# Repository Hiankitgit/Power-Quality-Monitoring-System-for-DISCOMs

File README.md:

# Power Quality Monitoring System for DISCOMs

## 📌 Overview
A low-cost, embedded diagnostic node designed for electricity distribution networks (DISCOMs). This system is engineered to detect sub-threshold power quality anomalies that are typically invisible to conventional protection devices. 

The hardware acts as a unified motherboard, integrating microcontrollers, analog voltage sensing, and industrial RS-485 communication into a single robust node.

## 🔌 Hardware Architecture
The custom PCB functions as a docking station utilizing pre-built modules and discrete through-hole components:
*   **Microcontrollers:** Arduino Uno & STM32 Blue Pill
*   **Voltage Sensing:** ZMPT101B AC voltage transformer module
*   **Communication:** MAX485 (TTL-to-RS485 transceiver) for node-level fault reporting
*   **Safety Infrastructure:** 220V AC mains are wired directly into the ZMPT module terminals, keeping high-voltage traces entirely isolated from the custom 5V logic board.

## 🛠️ PCB Design & Fabrication
Designed entirely in **KiCad**, the board layout was heavily optimized for DIY in-house manufacturing.
*   **Clearances & Traces:** Passed stringent DRC with 0.2mm minimum clearance. Main 5V and GND power rails are thickened (0.8mm) to prevent voltage drops across the docked modules.
*   **Routing Logic:** Verified intermediate node routing (including daisy-chained parallel capacitors) with 45-degree smoothed traces to prevent acid traps.
*   **Fabrication Method:** Specifically routed to support the **toner transfer etching** method on a blank copper clad board. A 1:1 scale mirrored PDF and standard Gerber `.zip` are provided in the `/fabrication` directory.

## 🖼️ Board Previews

# 💻 Firmware: Power Quality Monitoring Node

⚠️ **Status: Work In Progress (Fine-Tuning Phase)**

This directory contains the source code for the Arduino Uno and STM32 microcontrollers. 

### Current Development Focus
The baseline hardware communication is established, and we are actively calibrating the embedded signal processing algorithms. 
Current tasks include:
* Fine-tuning the ZMPT101B analog-to-digital (ADC) sampling windows.
* Implementing isolation and classification logic for 4 distinct power fault types.
* Formatting the RS-485 serial packet structure for reliable data transmission to DISCOMs.

Code will be updated regularly as the fault classification algorithms are finalized.

## 👥 Team & Credits
This system is being developed as an undergraduate academic group project by ECE Group 7 (2023–2027) under the supervision of Dr. Prachi Choudhary[cite: 8].

*   **Ankit** (23001003019) – Hardware Architecture & Lead PCB Design[cite: 3]
*   **Ashish** (23001003026)[cite: 3]
*   **Ayush Dahiya** (23001003028)[cite: 3]
*   **Ayush Maan** (23001003029)[cite: 3]
*   **Bhoomi** (23001003032)[cite: 3]

---
*Note: This repository contains the complete KiCad project files (`.kicad_pro`, `.kicad_sch`, `.kicad_pcb`), manufacturing drill/Gerber files, and firmware source code.*

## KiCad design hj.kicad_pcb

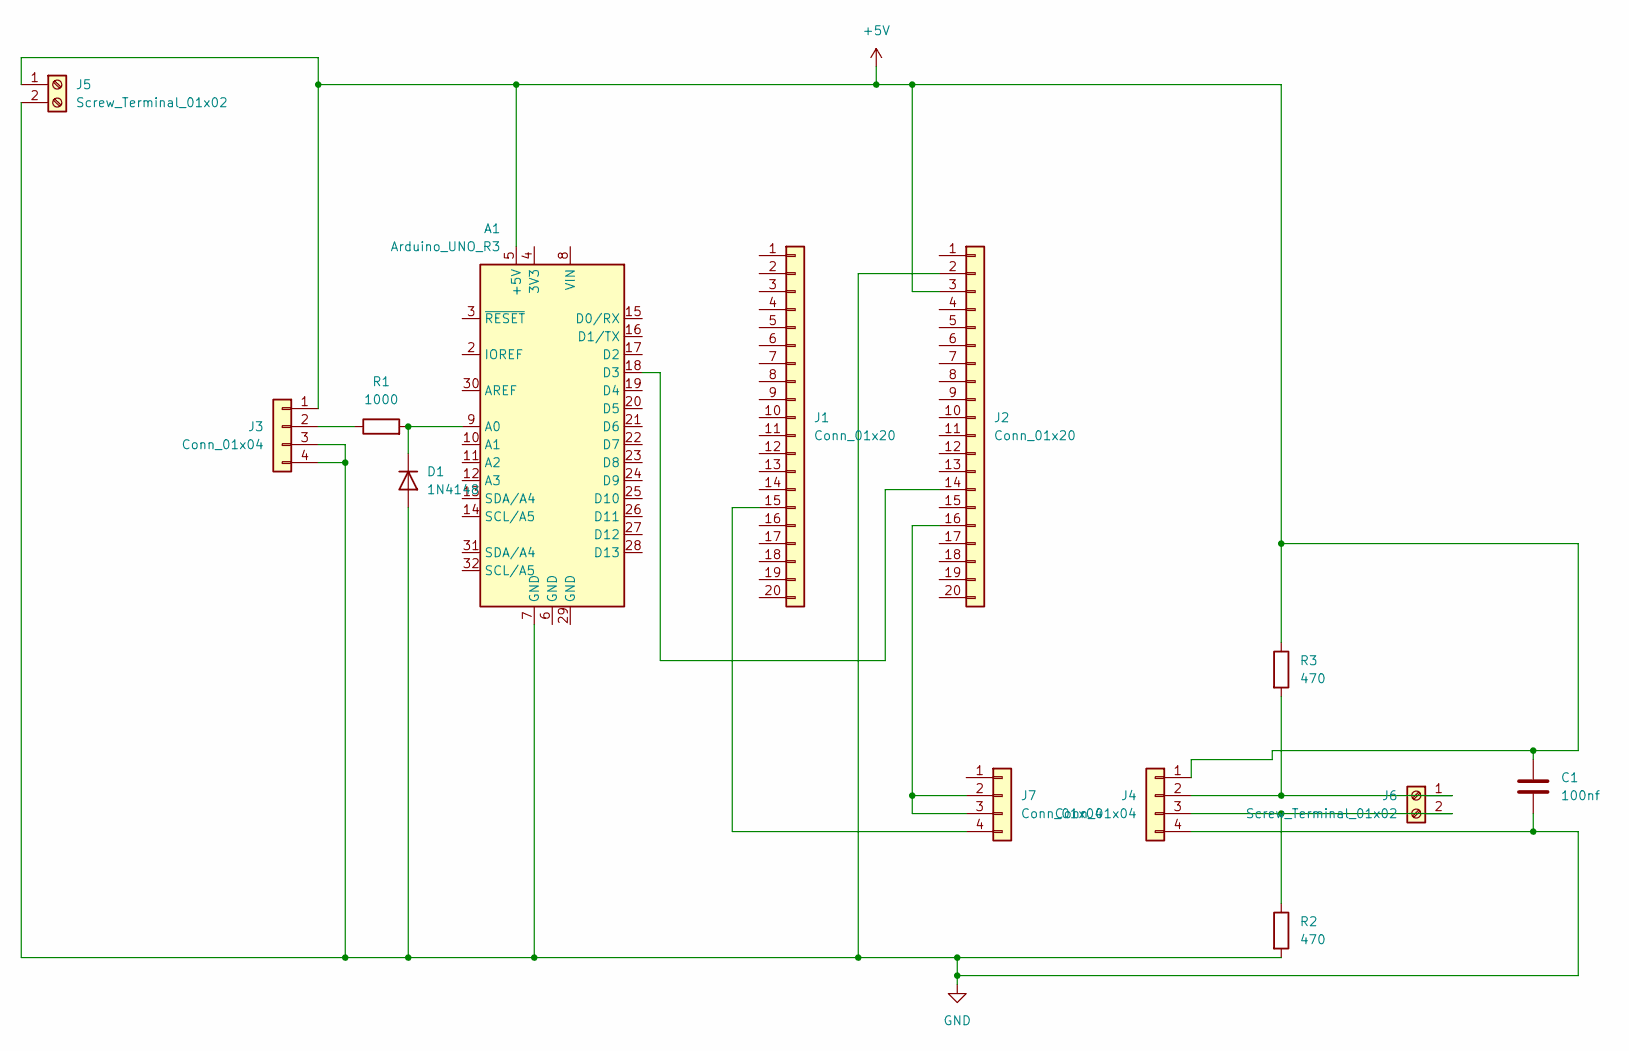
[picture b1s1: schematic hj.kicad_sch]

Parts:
A1: Arduino_UNO_R3
C1: 100nf; C_Disc_D5.0mm_W2.5mm_P5.00mm
D1: 1N4148; D_DO-35_SOD27_P7.62mm_Horizontal
J1, J2: Conn_01x20; PinSocket_1x20_P2.54mm_Vertical
J3, J4, J7: Conn_01x04; PinSocket_1x04_P2.54mm_Vertical
J5, J6: Screw_Terminal_01x02; TerminalBlock_Phoenix_MKDS-1,5-2-5.08_1x02_P5.08mm_Horizont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
R1: 1000; R_Axial_DIN0207_L6.3mm_D2.5mm_P10.16mm_Horizontal
R2, R3: 470; R_Axial_DIN0207_L6.3mm_D2.5mm_P10.16mm_Horizontal

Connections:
+5V: A1.5 (+5V), C1.1, J2.3, J3.1, J4.1, J5.1, R3.1
GND: A1.7 (GND), C1.2, D1.2 (A), J2.2, J3.3, J3.4, J4.4, J5.2, R2.2
unnamed: A1.9 (A0), D1.1 (K), R1.2
unnamed: A1.18 (D3), J2.14
unnamed: J1.15, J7.4
unnamed: J2.16, J7.2, J7.3
unnamed: J3.2, R1.1
unnamed: J4.2, J6.1, R3.2
unnamed: J4.3, J6.2, R2.1

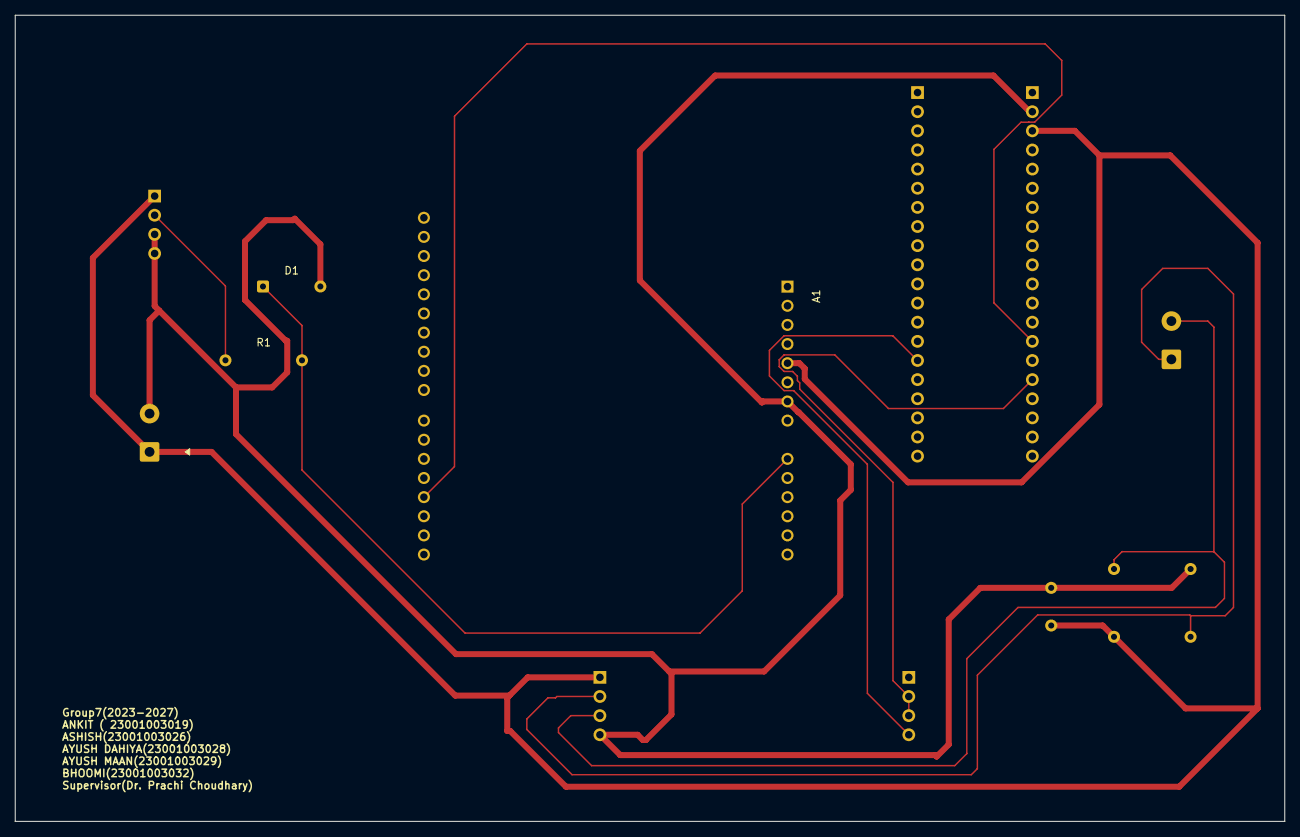
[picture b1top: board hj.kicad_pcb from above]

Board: 2 copper layers, 168.5 x 107.0 mm, 13 parts (0 on the bottom side), 9 nets.
